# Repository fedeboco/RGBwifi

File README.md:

# ESP 8266 Wi-Fi RGB LED Strip Controller

### Idea
- Local network WiFi server.
- Browser GUI for color selection.
- Analog on-board hue-color and brightness selection.
- Multiple board control (not implemented yet).

### WiFi Configuration Example

Connecting to an specific Wi-Fi network will be possible by fisrt connecting to an Access Point created by the ESP and sending the credentials using that network. The device stores the settings in EEPROM and restarts with the desired network configured.

### Use Example

### Software and Dependencies
- Arduino IDE 1.8.3
- ESP8266 Board Driver by EP8266 Community. v2.5.0. https://github.com/esp8266/Arduino
- ESP8266 Web Server v1.0.0
- JavaScript Color Picker http://jscolor.com/

### Schematic

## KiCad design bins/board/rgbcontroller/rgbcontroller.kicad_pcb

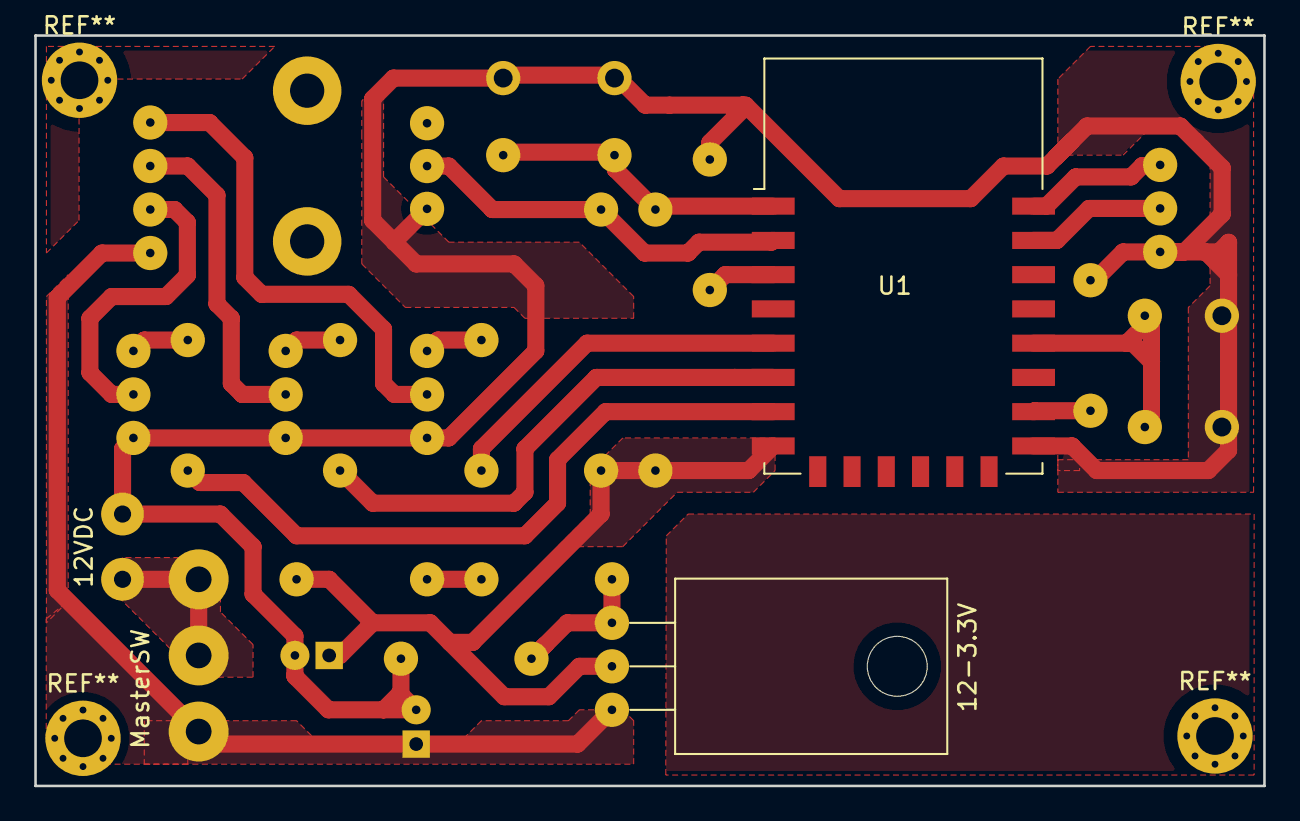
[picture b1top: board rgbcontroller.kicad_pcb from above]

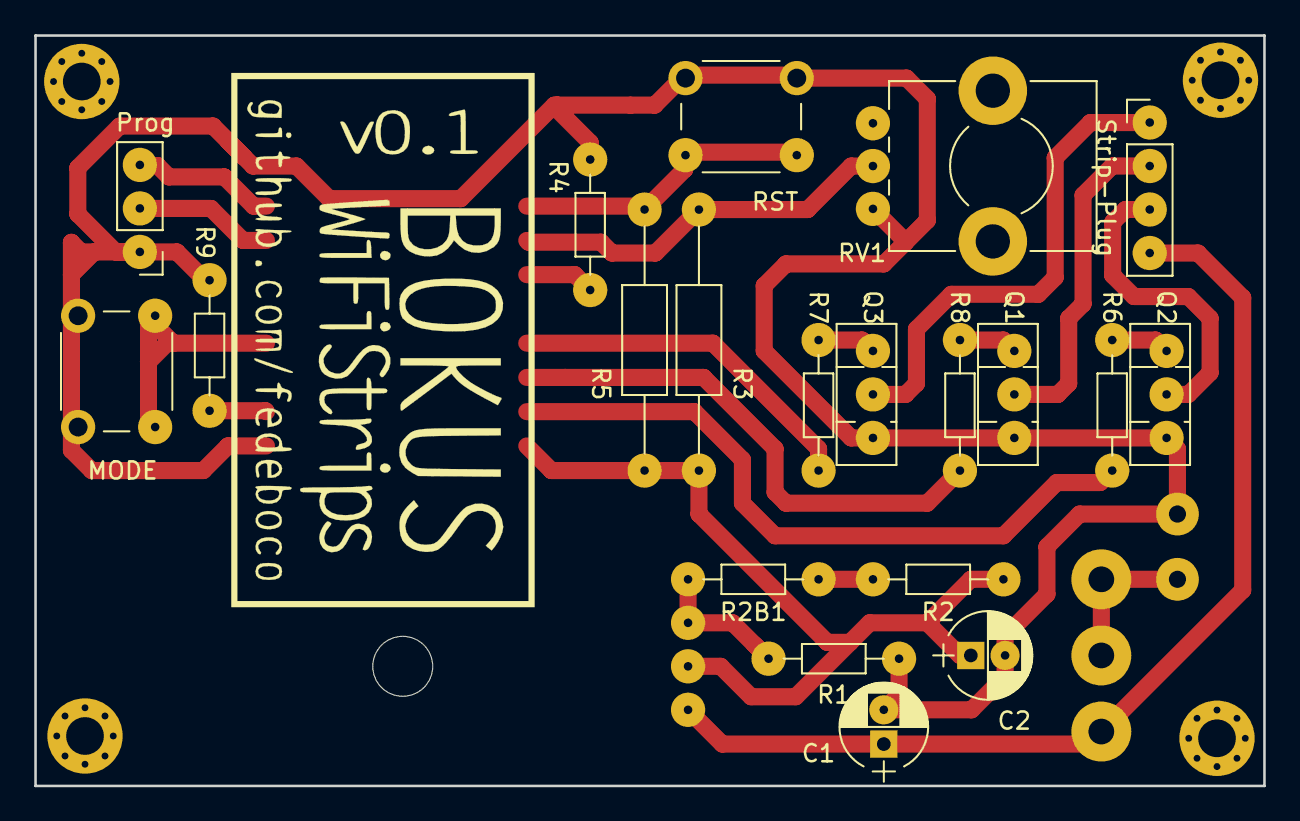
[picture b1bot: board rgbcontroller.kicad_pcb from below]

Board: 2 copper layers, 71.8 x 43.8 mm, 24 parts (20 on the bottom side), 22 nets.

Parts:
12-3.3V: LM317_3PinPackage; TO-220-3_Horizontal
12VDC: Barrel_Jack_MountingPin; SolderWirePad_2x_1mmDrill
C1: 0.1u; CP_Radial_D5.0mm_P2.00mm
C2: 10u; CP_Radial_D5.0mm_P2.00mm
MODE: SW_Push; SW_PUSH_6mm_h7.3mm
MasterSW: SW_SPDT; SolderWirePad_3x_1-5mmDrill
Prog: Conn_01x03_MountingPin; Pin_Header_Straight_1x03_Pitch2.54mm
Q1, Q2, Q3: BD139; TO-126_Vertical
R1: 390; R_Axial_DIN0204_L3.6mm_D1.6mm_P7.62mm_Horizontal
R2, R2B1: 120; R_Axial_DIN0204_L3.6mm_D1.6mm_P7.62mm_Horizontal
R3: 22k; R_Axial_DIN0207_L6.3mm_D2.5mm_P15.24mm_Horizontal
R4, R9: 10k; R_Axial_DIN0204_L3.6mm_D1.6mm_P7.62mm_Horizontal
R5: 10k; R_Axial_DIN0207_L6.3mm_D2.5mm_P15.24mm_Horizontal
R6, R7, R8: 1k; R_Axial_DIN0204_L3.6mm_D1.6mm_P7.62mm_Horizontal
RST: RST; SW_PUSH_6mm_h7.3mm
RV1: 9k; Potentiometer_Alps_RK09K_Horizontal
Strip-Plug: Conn_01x04_MountingPin; Pin_Header_Straight_1x04_Pitch2.54mm
U1: ESP-12E

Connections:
+12-strip: 12-3.3V.3, C1.1, MasterSW.1, Strip-Plug.4
/+3.3V: 12-3.3V.2, C2.1, R2.2, R3.2, R5.1, U1.8
B-strip: Q3.2, Strip-Plug.1
G-strip: Q2.2, Strip-Plug.3
GND: 12VDC.2, C1.2, C2.2, MODE.1, Prog.1, Q1.1, Q2.1, Q3.1, R1.2, R4.2, R9.2, RST.2, RV1.1, U1.15
unnamed: 12VDC.1, MasterSW.2, MasterSW.3
unnamed: Prog.2, U1.21
unnamed: Prog.3, U1.22
unnamed: Q1.3, R8.2
unnamed: Q2.3, R6.2
unnamed: Q3.3, R7.1
unnamed: 12-3.3V.1, R1.1, R2B1.1
unnamed: R2.1, R2B1.2
unnamed: R3.1, RV1.2, U1.2
unnamed: R4.1, U1.3
unnamed: R5.2, RST.1, U1.1
unnamed: R6.1, U1.7
unnamed: R7.2, U1.5
unnamed: R8.1, U1.6
unnamed: R9.1, U1.16
unnamed: MODE.2, U1.18
R-strip: Q1.2, Strip-Plug.2

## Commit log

2020-04-03 Initial setup and connection
2020-04-03 Better serial display
2020-04-04 RGB strobe, RGB by index in hue
2020-04-04 Potentiometer RGB control
2020-04-04 Improved stability and color intensity
2020-04-05 color picker
2020-04-07 WiFi, Manual, Strobe and Brightness modes
2020-04-08 WiFi mode enabled. Simple webpage on browser using jscolor
2020-04-08 colour to color
2020-04-08 Soft Brightness
2020-04-10 Button hold check, Network Config Class
2020-04-11 Access Point Server working.
2020-04-11 WiFi Config Site and Request from Browser
2020-04-11 Network Configuration and Restart Fully Functional
2020-04-14 Example Images
2020-04-14 Schematic
2020-06-18 PCB adjustments
2020-06-19 Minor screws adjustments
